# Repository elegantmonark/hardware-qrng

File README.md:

# Hardware QRNG Investigation

This is my attempt to investigate whether a circuit built around a reverse biased green LED, an amplifier and an Arduino can serve as a physical entropy source. ED-1 used an LM358; the newer ED-4A PCB specifies an MCP6002. The [contents](#contents) and [repository guide](#repositoryguide) point to the measurements, circuit revisions and analysis. Enjoy your time here :)) (BE SURE TO READ THE "IMPORTANT" SECTIONS!)

**Author:** Trishan Biswas  
**Project started:** December 2025  
**First complete demonstrator and dataset:** April 2026

| ED-1 bit balance and software comparison | ED-2 latest breadboard build |
|:---:|:---:|
|  |  |
| ED-1 output compared with a deterministic Mersenne Twister control. Similar results do not establish physical origin or security. | Latest documented ED-2 arrangement, retained as a development build rather than a validated entropy source. |

**ED-4A signal path simulation:** A small test signal is amplified to the expected
Arduino input range in an approximate ngspice model. The LED source remains to
be measured. [Simulation details](hardware/ED-4/pcb/ED4-A/simulation/README.md).

## Contents

- [MATLAB analysis](#matlab) · [ED-4A Arduino PCB](#ed4pcb) · [ED-4A PCB views](#pcbviews) · [ngspice checks](#ngspicechecks) · [Overview](#overview)
- [Quick terminology](#terminology) · [Development](#development) · [ED 1 results](#ed1results) · [Quantum triggers and a possible TRNG](#quantumtriggers) · [Limitations](#limits)
- [ED 2 circuit](#ed2circuit) · [ED 3 circuit](#ed3circuit) · [ED-4 PCB and printed enclosure](#ed4enclosure) · [Hardware photographs](#photographs) · [Repository guide](#repositoryguide)
- [Next work](#nextwork) · [Licence](#licence) · [Reproducing the analysis](#analysis) · [Collecting new data](#collection)

## MATLAB analysis

I used MATLAB to examine the original million sample Arduino capture through
signal traces, ADC distributions, a Hann windowed FFT, autocorrelation and bit
balance across consecutive blocks. The analysis runs without extra toolboxes.

The proportion of ones is 0.497767, but the raw ADC correlation at lag 1 is
0.9057 and the strongest spectral component repeats every 14.87 samples.
The extracted bits look nearly balanced while the original signal has clear
structure. That distinction guides the next round of circuit measurements.

The [MATLAB source and instructions](software/matlab/README.md) explain how to
repeat the analysis. The [saved results](results/ED-1/matlab/README.md) include
the report, correlation CSV and editable figure. The MATLAB R2026b Update 1
results matched the Python audit, including all 101 exported correlation rows.
These are descriptive checks, not proof of quantum origin or secure entropy.

## ED-4A Arduino PCB

The first ED-4 PCB is a two layer, 89 by 52 mm board for the enclosure already
printed. It brings the buffered reference, source selector, signal amplifier
and Arduino interface together with seven test points and a bottom ground fill.
The design uses through hole parts for assembly and inspection.

The [editable KiCad project](hardware/ED-4/pcb/ED4-A/ED4_A_Arduino.kicad_pro),
[schematic](hardware/ED-4/pcb/ED4-A/drawings/ED4_A_schematic.pdf) and
[board guide](hardware/ED-4/pcb/ED4-A/README.md) are available for review.
The revision B layout uses an MCP6002 and a standard 100k and 1k gain network.
It passes KiCad ERC, DRC and schematic parity checks. Circuit validation and
populated enclosure fit remain pending. The [purchase BOM](hardware/ED-4/pcb/ED4-A/BOM.csv)
records the chosen components.

I have also included the [JLCPCB Gerber ZIP, assembly BOM and placement file](hardware/ED-4/pcb/ED4-A/jlcpcb/README.md).
That assembly option covers 11 components. R3, R4, R6 and D1 would be fitted
by hand because they were unavailable in the assembly inventory. The removable
JP1 shunt is separate too. I may instead order the bare PCB and fit all the
components myself.

I also ran an [ngspice signal path check](hardware/ED-4/pcb/ED4-A/simulation/README.md)
with the PCB component values and a small injected test signal. The approximate
model shows the expected reference and gain at the Arduino input. It does not
model the LED noise or validate the entropy source.

ED-4A uses an external Arduino with a 5 V ADC interface. ED-4E is the planned
ESP32 revision and will have its own ADC and power interface review.

## ED-4A PCB views

These are KiCad views of the revision B design. They show the intended board
and component positions before manufacture. The 3D renders show R3, R4, R6
and D1 in place, although those parts are omitted from the optional JLCPCB
assembly order. C4 appears as a footprint because its 3D model is not shown.
The LED model is red in these views, but the BOM specifies a green LED.

### Routed layout

### Component renders

| Top view | Angled view |
|:---:|:---:|
|  |  |

The renders show the planned layout, not a built board or a confirmed fit in
the printed enclosure.

## ngspice checks

I used ngspice to test the ED-4A analogue path with known inputs before
building the board. The [netlists, figures and method](hardware/ED-4/pcb/ED4-A/simulation/README.md)
are in the simulation folder. They use the PCB values and an approximate op amp
model. None of these runs models the LED noise or proves that the circuit will
produce useful entropy.

The first check used a 2 mV peak signal at 1 kHz and showed about 100 times
gain at the Arduino input. I then grounded the input and added a 100 mV peak,
100 Hz ripple to the 5 V rail. In that model A0 still moved by about 160 mV
peak, so the actual supply and grounded control will need careful measurement.

I also compared 2 mV and 40 mV peak test inputs. The smaller signal stayed
within the Arduino input range, while the larger one reached both output
limits in the model. The LED signal amplitude has not been measured yet.

## Overview

The project is organised into four stages. ED stands for Entropy Demonstrator;
the table distinguishes the completed work, archived prototypes and planned builds.

| Stage | Purpose | Current state |
|---|---|---|
| **ED-1** | Prove that the full path from circuit to saved data and analysis could work | Complete and preserved |
| **ED-2** | Explore a documented two-stage analogue path and acquisition process | Completed and preserved as a breadboard investigation; reference loading found during bring-up and recorded |
| **ED-3** | Validate a simpler buffered reference circuit on breadboard, with optional perfboard transfer afterwards | Design documented; assembly and validation pending |
| **ED-4** | Custom PCB for the existing printed enclosure | ED-4A Arduino layout available for review; 89 by 52 mm; bench and populated fit checks pending. ED-4E ESP32 revision planned |

The name QRNG describes the research direction. The present evidence supports an experimental physical entropy source, not a certified quantum random number generator or a source suitable for cryptographic use.

The investigation asks three practical questions:

1. Does the circuit produce measurable physical noise?
2. Can useful digital bits be extracted from it consistently?
3. Do the results survive repeat captures, restarts and control experiments?

Statistical tests can describe a bitstream, but they cannot identify its physical origin on their own. The circuit, sampling process and possible interference must be studied alongside the output.

## Quick terminology

| Term | Meaning in this project |
|---|---|
| **Entropy source** | A physical process being investigated as a possible source of unpredictable variation |
| **ADC reading** | A number produced when the Arduino converts the measured circuit voltage into a digital value |
| **Least significant bit** | The final binary digit of an ADC reading, recorded here as a candidate random bit |
| **Bitstream** | The resulting sequence of zeros and ones |
| **Software control** | A deterministic Mersenne Twister sequence used for comparison, not a NIST reference generator |
| **ED** | Entropy Demonstrator |

The analysis checks balance, repetition, correlation and stability. A balanced output alone does not prove that the signal is quantum or secure.

## Development

I began the project in December 2025 because it combined semiconductor physics, analogue electronics, microcontroller sampling and Python analysis in one experiment.

In April 2026, ED-1 became the first complete demonstrator. It produced a saved sequence of one million ADC readings and one least significant bit from each reading. I then built a software control, generated comparison figures and ran exploratory statistical tests.

> [!IMPORTANT]
> The first result looked promising because the extracted bits were close to balanced. A later audit showed that the raw ADC sequence contained strong correlation and a repeating component. This did not make ED-1 useless. It made ED-1 a clear baseline and showed what the next version needed to improve.

ED-2 kept the original LED source idea but added a defined midpoint reference, two amplifier stages, clearer bias paths, supply decoupling and output protection. During systematic bring-up, the Stage A reference branch pulled the unbuffered midpoint from approximately 2.5 V to approximately 1.3 V. That result is preserved as part of the engineering record rather than presented as a validated improvement.

ED 3 starts again with a simpler topology. Its documented breadboard uses one
LM358 section to buffer the midpoint and the other as a signal amplifier. The
ED-4 PCB revision B uses a pin compatible MCP6002 and revised resistor values
to reduce input bias error. That component change needs its own bench checks.
After breadboard validation, the ED 3 circuit may also be transferred to
perfboard and checked again. ED-4 has a nominal 89 by 52 mm outline for the
enclosure already printed. The earlier
bare perfboard fit check establishes a starting board envelope; PCB tolerances,
component clearance and connector access still need checking.

## ED 1 results

The preserved April 2026 capture contains 1,000,000 samples.

| Measurement | Result |
|---|---:|
| Ones | 497,767 |
| Zeros | 502,233 |
| Proportion of ones | 0.497767 |
| Binary Shannon entropy | 0.9999856 bits per bit |
| Most common value estimate | 0.9935713 bits per bit |
| Raw ADC range | 0 to 760 |
| Raw ADC lag 1 correlation | 0.9057 |
| Dominant raw period | approximately 14.87 samples |
| Extracted bit lag 1 correlation | 0.00119 |

The bit balance was encouraging, but the raw ADC correlation showed that the analogue signal contained substantial structure. The exploratory NIST STS run also reported failures in Frequency, Runs and forward Cumulative Sums. These results are kept in the repository because they are part of the engineering record.

The full interpretation is recorded in [`docs/validation.md`](docs/validation.md).

## Quantum triggers and a possible TRNG

The idea is to use noise from a reverse biased semiconductor junction as the
physical input to a true random number generator (TRNG). Zener tunnelling is a
quantum process in which carriers cross the junction barrier. Avalanche
breakdown instead multiplies carriers through impact ionisation; a small,
stochastic carrier event can seed a much larger cascade. That makes tiny events
measurable in a suitable device. Signal size and entropy are different things,
though: a large, changing voltage is not automatically unpredictable.
[Analog Devices' breakdown explanation](https://wiki.analog.com/university/courses/electronics/text/chapter-14#zener_diodes)
distinguishes the Zener and avalanche regimes.

ED-4A biases an ordinary green LED through 10 MΩ from 3.3 V. I have not measured
its reverse current or shown that this LED reaches Zener or avalanche breakdown
at that bias. The board's amplifier has a simulated gain of about 100 for a
known test signal; an additional avalanche multiplication factor has not been
measured. For now this is a **candidate physical TRNG with a possible quantum
contribution**, rather than an established QRNG. [Diode tunnelling has been used
in a demonstrated QRNG](https://doi.org/10.1103/PhysRevApplied.11.034060), but
that result does not establish the mechanism in this LED.

The useful experiment is to measure the LED voltage and reverse current, then
compare the source with grounded input, resistor and covered LED controls over
repeat captures. That will show whether the junction adds measurable variation
before making a claim about where the unpredictable part comes from. The
[validation notes](docs/validation.md) spell out the remaining checks.

## Limitations

The present data cannot separate junction noise from Johnson–Nyquist noise in
resistors, low frequency flicker noise, amplifier and ADC noise, or movement of
the power supply. Thermal and flicker noise can be genuinely stochastic; the
issue is attributing the measured bits specifically to a quantum junction
process. Supply ripple and coupled interference can add repeatable structure
that looks like activity at the ADC. The [ngspice grounded-input check](hardware/ED-4/pcb/ED4-A/simulation/README.md)
shows why the reference and supply need measuring on the real board.

ED-1 contains one capture with strongly correlated raw ADC readings. ED-2
exposed a reference loading fault. ED-3 and the ED-4A PCB still need source and
control measurements. Near equal numbers of zeros and ones, a high marginal
Shannon entropy, or a large analogue signal do not establish an independent
entropy rate. [NIST SP 800-90B](https://doi.org/10.6028/NIST.SP.800-90B)
provides a framework for characterising an entropy source; this project has
not completed that validation.

> [!CAUTION]
> No output from this repository should be used for cryptographic keys, authentication, gambling, financial decisions or safety critical systems.

The [detailed limitations](docs/limitations.md), [safety notes](docs/safety.md)
and [security notes](SECURITY.md) give the test conditions and remaining gaps.

## ED 2 circuit

ED-2 uses the following signal path:

1. A green LED is connected as the proposed physical noise source.
2. A 2.5 V midpoint reference supports operation from a single 5 V supply.
3. Two LM358 noninverting stages amplify the alternating component of the signal.
4. A protected output feeds Arduino input A0.
5. The Arduino records each raw ADC code and its least significant bit.
6. A steady D7 indicator shows that the sampler is running without switching for every recorded bit.

The exact component values, breadboard positions, expected voltages and assembly order are documented in [`circuit.md`](circuit.md). The matching sampler is stored at [`firmware/ED-2/entropy_sampler_ed2.ino`](firmware/ED-2/entropy_sampler_ed2.ino).

ED-2 produced live ADC readings, but systematic probing exposed reference loading in the assembled topology. ED-2 is completed and preserved as an investigation with a documented design fault. It has no published validation dataset and is not a verified entropy source.

## ED 3 circuit

ED-3 uses a buffered midpoint reference and one signal amplifier. The reduced
topology removes the second signal-gain stage and prevents the gain network from
directly loading the 10 kOhm midpoint divider.

The proposed component values, electrical netlist and staged bring-up sequence
are documented in [`hardware/ED-3/circuit.md`](hardware/ED-3/circuit.md). The
matching sampler is stored at
[`firmware/ED-3/entropy_sampler_ed3.ino`](firmware/ED-3/entropy_sampler_ed3.ino).
ED-3 will not be described as working until its reference, amplifier baseline,
source controls and repeat captures have been checked.

An optional perfboard version remains part of ED 3. It follows breadboard
validation and must repeat the electrical checks and control captures after
transfer.

## ED-4 PCB and printed enclosure

ED-4 combines a custom routed PCB with the existing two part enclosure. The base
was printed successfully, and an 89 by 52 mm bare perfboard fits between its
locating features. The PCB will use that nominal envelope, with a target
thickness of 1.6 mm. Its final fit must account for print tolerances, support
rails, solder joints, component height and cable access.

| Dimension | Value |
|---|---:|
| Nominal PCB target | 89 by 52 mm, 1.6 mm thick |
| Internal space | 105 by 68 by 34 mm |
| Approximate assembled exterior | 109.8 by 72.8 by 40 mm |
| Board support height | 8 mm |
| Clearance above the board | approximately 24.4 mm |
| Cable opening | 26 by 12 mm |

The existing cable opening was sized for an Arduino harness. The final PCB
connector and acquisition interface will follow the validated ED 3 circuit.

The [PCB plan](hardware/ED-4/pcb-plan.md) records the mechanical constraints,
intended features and checks required before fabrication.

The [ED-4A Arduino PCB](hardware/ED-4/pcb/ED4-A/README.md) is the current routed
review design. ED-4E will cover ESP32 separately. The board outline is shared;
the ADC and power interfaces must be reviewed for each revision.

The editable source, printable files, dimensions and print guidance are available in the [ED-4 CAD directory](hardware/ED-4/cad/README.md).

The current KiCad evidence is the [ED-4A schematic and routed PCB](hardware/ED-4/pcb/ED4-A/README.md).
The layout passes ERC, DRC and schematic parity checks. The earlier unfinished
perfboard placement draft has been superseded by this design.

| Printed ED-4 enclosure base | Initial perfboard fit check |
|:---:|:---:|
|  |  |
| The first physical print of the enclosure base and internal locating features. | An 89 by 52 mm bare perfboard establishing the initial envelope for the planned PCB. |

## Hardware photographs

The photographs keep the demonstrators visually separate so their wiring and mechanical progress cannot be mistaken for the same revision.

| ED-1 first demonstrator | ED-2 improved breadboard |
|---|---|
|  |  |
| Original breadboard used for the first complete acquisition and analysis path. | Wider view of the latest documented ED-2 breadboard with its Arduino connection. |

Additional views and captions are stored in the [ED-1 hardware notes](hardware/ED-1/README.md), [ED-2 hardware notes](hardware/ED-2/README.md) and [ED-4 enclosure notes](hardware/ED-4/README.md).

## Repository guide

| Location | Contents |
|---|---|
| [`data/`](data/README.md) | Preserved captures, controls and integrity hashes |
| [`docs/`](docs/development-log.md) | Development history, theory, limits, safety and validation plans |
| [`figures/ED-1/`](figures/ED-1/) | Figures generated from the April 2026 capture |
| [`firmware/`](firmware/README.md) | Arduino samplers separated by demonstrator |
| [`hardware/`](hardware/README.md) | Photographs, build records, the ED-3 circuit and ED-4 CAD |
| [`results/`](results/README.md) | The ED-1 audit and exploratory statistical output |
| [`software/`](software/) | Collection, analysis, comparison and extraction tools |
| [`tests/`](tests/) | Data, link, asset, analysis and CAD integrity tests |

The artwork made from the ED-1 bits is prepared as a [separate Bitstream Art project](https://github.com/elegantmonark/qrng-bitstream-art).

## Next work

1. Assemble ED-3 in tested stages, beginning with the buffered reference.
2. Record the final component values, node checks and build photographs.
3. Capture ED-3 controls and source runs across independent restarts.
4. Compare its raw signal structure, bias, correlation and stability with ED-1.
5. Establish a conservative entropy estimate before introducing conditioning.
6. Select the acquisition architecture from evidence; an Arduino, ESP32, or external ADC must not be treated as the entropy source.
7. Optionally transfer the validated ED 3 circuit to perfboard and repeat its checks.
8. Build the ED-4 PCB within the printed enclosure's 89 by 52 mm board envelope.

## Licence

The hardware, analysis and documentation are released under the Apache License 2.0 in [`LICENSE`](LICENSE).

## Reproducing the analysis

Install the Python dependencies from the repository root:

```bash
python -m pip install -r requirements.txt
```

Run the repository tests:

```bash
python -m unittest discover -s tests -v
```

Regenerate the ED-1 diagnostics and comparison:

```bash
python software/analyser.py
python software/compare.py
```

For the MATLAB version, see the [analysis section](#matlab) and its
[run instructions](software/matlab/README.md).

The exploratory NIST wrapper requires a separately installed NIST STS executable. Read [`docs/validation.md`](docs/validation.md) before interpreting its output.

## Collecting new data

After ED-3 passes bring-up, upload the ED-3 sampler, confirm the serial port and run:

```bash
python software/collector.py --port COM3 --samples 1000000
```

Replace `COM3` with the port used by the Arduino. The collector writes a new timestamped CSV and a JSON metadata file under `data/ED-3/runs/`. A capture should not be published until the circuit values, firmware version, conditions and file hash have been recorded.

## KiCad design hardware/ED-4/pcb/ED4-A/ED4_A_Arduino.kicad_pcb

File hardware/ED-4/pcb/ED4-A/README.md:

# ED4 A Arduino prototype, revision B

This board carries the proposed ED 3 buffered reference and signal amplifier
inside the printed ED 4 enclosure. It uses through hole parts and an external
Arduino for power and data capture. The PCB is 89 by 52 mm and 1.6 mm thick.

The layout is a review prototype. The circuit has not yet been validated on
breadboard or PCB, and populated fit has not been checked in the actual print.
Check the circuit and enclosure fit before ordering a populated prototype.

## Open the project

Open [ED4_A_Arduino.kicad_pro](ED4_A_Arduino.kicad_pro) in KiCad 10. The
[schematic](ED4_A_Arduino.kicad_sch) and [PCB](ED4_A_Arduino.kicad_pcb) are
editable. The circuit values follow the current ED 3 proposal, with a local
10 uF supply capacitor and a source/control selector added for testing. This
revision uses an MCP6002 op amp and standard resistor values chosen for the
actual circuit rather than parts already on hand.

## Files for review

| File | Purpose |
| --- | --- |
| [Schematic PDF](drawings/ED4_A_schematic.pdf) | Connected circuit and pin labels |
| [Assembly PDF](drawings/ED4_A_assembly.pdf) | Component positions and enclosure rail strips |
| [BOM](BOM.csv) | Selected manufacturer parts and board footprints |
| [JLCPCB order files](jlcpcb/README.md) | Gerber ZIP, assembly BOM and placement file |

KiCad 10.0.1 reports 0 ERC violations, 0 DRC violations, 0 unconnected items
and 0 schematic parity issues. An independent pin contract check agreed with
the schematic and board. These checks do not replace bench validation.

The [ngspice signal path check](simulation/README.md) uses an injected test
signal and an approximate op amp model to check the intended reference and
amplifier response. It does not model the LED noise or validate the PCB in
hardware.

The full BOM lists the original part choices. The JLCPCB assembly BOM uses
available alternatives for C1, C2 and C3, and leaves R3, R4, R6 and D1 for
hand assembly. Check part selection and the actual enclosure fit before
ordering. A successful layout check does not establish that the LED produces
useful entropy in this circuit.

## Arduino connector

J1 is a straight 2.54 mm pin header. Pad 1 is square and the signals are marked
on the board. Check pin numbers in KiCad before attaching the harness.

| J1 pin | Signal | Connection |
| --- | --- | --- |
| 1 | 5V | Arduino 5 V supply |
| 2 | 3V3 | Arduino 3.3 V source bias supply |
| 3 | GND | Common ground |
| 4 | A0 | Analogue output for a 5 V Arduino ADC interface |

Arduino AREF is left disconnected. Do not connect the output directly to an
ESP32 ADC. The future ED4 E revision will handle that interface separately.

## Source and control selector

JP1 is a three pin header with one removable shunt. Change its position with
power disconnected.

| Shunt | Connection | Use |
| --- | --- | --- |
| Pins 1 and 2 | LED source to the coupling capacitor | Source capture |
| Pins 2 and 3 | Coupling capacitor input to ground | Grounded AC input control |
| No shunt | Coupling capacitor input open | Open input diagnostic only |

The grounded control changes the input condition and does not isolate every
noise contribution. D1 remains biased through R3 in either shunt position.
Use separate covered LED, resistor control and restart captures as well.

D1 pad 1 is the cathode and pad 2 is the anode. Its reverse biased connection
follows the experimental ED 3 circuit. The listed Kingbright WP7113GD is a
physical part choice, not a validated entropy source. Its reverse behavior at
3.3 V must be measured before a functional claim can be made.

## Test points

| Point | Signal |
| --- | --- |
| TP1 | Raw midpoint reference |
| TP2 | Buffered midpoint reference |
| TP3 | LED source node |
| TP4 | Amplifier input |
| TP5 | Amplifier output before R7 |
| TP6 | Arduino A0 output after R7 |
| TP7 | Ground |

Probing the high impedance source node can load it. Record the probe and
measurement setup when interpreting the source signal.

## Mechanical review

The board outline matches the envelope used for the enclosure fit check.
The marked rail contact strips are on the drawing layer. Check solder joints
against the rails, components against the corner guides and lid, and the cable
bend against the 26 by 12 mm opening. No mounting holes have been assumed.

The [enclosure CAD](../../cad/README.md) preserves the existing printed geometry.
Two rule areas prohibit pads and vias where the printed rails touch the board.
The bottom copper layer has a filled ground return.

## Board mark

The front silkscreen carries a compact QRNG mark: a Q ring flowing into three
digital bit marks. It is an editable group named `QRNG logo` in the PCB editor.
The [SVG](../assets/qrng-logo.svg) is included for reuse in project documents.

## First bench checks

1. Check part values, U1 orientation, D1 polarity and capacitor polarity.
2. With the supply off, inspect for shorts and verify J1 pin order.
3. Power the board with current limiting and check the supply rails.
4. Measure TP1 and TP2. Confirm the reference remains stable under load.
5. Select the grounded AC control and check amplifier baseline and headroom.
6. Inspect for clipping or oscillation before connecting the Arduino ADC.
7. Compare source, control and restart captures using the original raw samples.

The nominal gain is 1 + 100k / 1k = 101. R4 is 100k and R7 is 1k. The
MCP6002 has much lower input bias than the earlier LM358 choice, which matters
for the high impedance input. Its offset still affects the baseline, so check
TP5 for clipping and stability. The [Microchip datasheet](https://ww1.microchip.com/downloads/aemDocuments/documents/MSLD/ProductDocuments/DataSheets/MCP6001-1R-1U-2-4-1-MHz-Low-Power-Op-Amp-DS20001733L.pdf)
documents the PDIP pinout and electrical limits. The schematic uses the
KiCad LM2904 graphical symbol because its three units have the same pin map;
the fitted component is the MCP6002-I/P in the BOM and PCB.

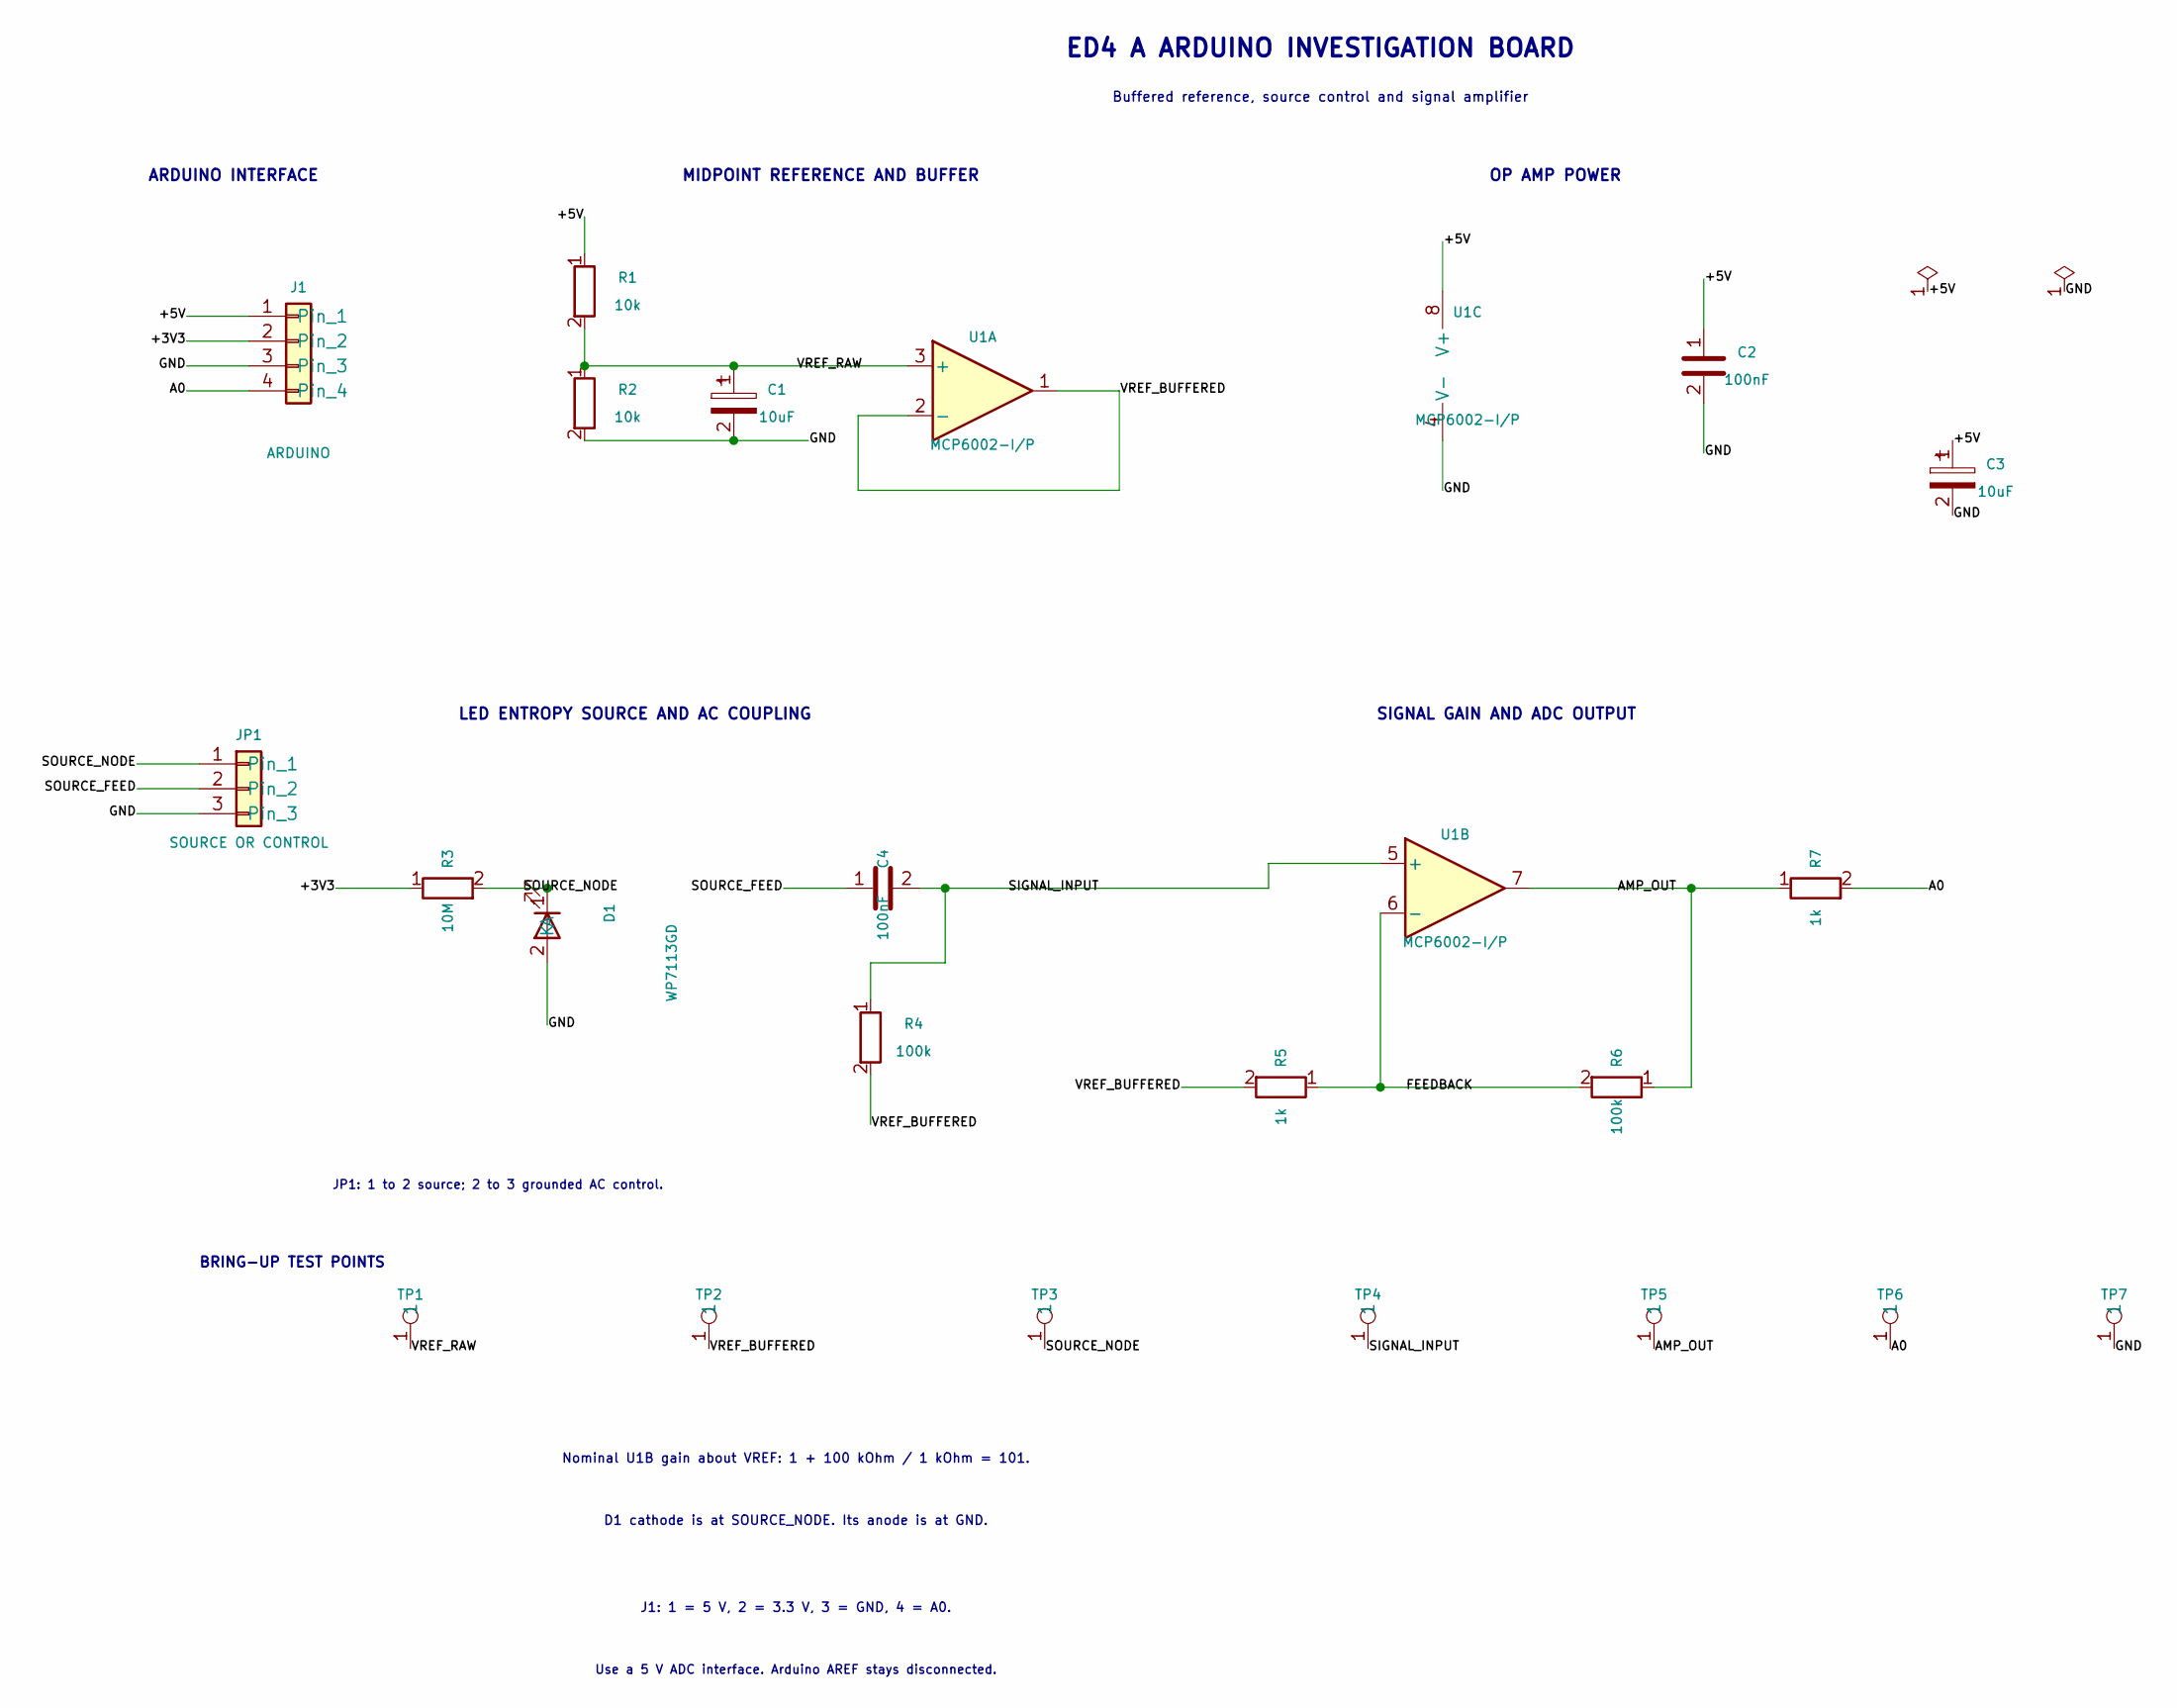
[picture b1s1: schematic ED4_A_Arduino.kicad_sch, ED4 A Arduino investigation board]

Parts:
C1, C3: 10uF; CP_Radial_D5.0mm_P2.00mm
C2: 100nF; C_Disc_D5.0mm_W2.5mm_P2.50mm
C4: 100nF; C_Rect_L7.2mm_W2.5mm_P5.00mm
D1: WP7113GD; LED_D5.0mm
J1: ARDUINO; PinHeader_1x04_P2.54mm_Vertical
JP1: SOURCE OR CONTROL; PinHeader_1x03_P2.54mm_Vertical
R1, R2: 10k; R_Axial_DIN0207_L6.3mm_D2.5mm_P10.16mm_Horizontal
R3: 10M; R_Axial_DIN0207_L6.3mm_D2.5mm_P10.16mm_Horizontal
R4, R6: 100k; R_Axial_DIN0207_L6.3mm_D2.5mm_P10.16mm_Horizontal
R5, R7: 1k; R_Axial_DIN0207_L6.3mm_D2.5mm_P10.16mm_Horizontal
TP1: VREF_RAW; TestPoint_THTPad_D2.0mm_Drill1.0mm
TP2: VREF_BUFFERED; TestPoint_THTPad_D2.0mm_Drill1.0mm
TP3: SOURCE_NODE; TestPoint_THTPad_D2.0mm_Drill1.0mm
TP4: SIGNAL_INPUT; TestPoint_THTPad_D2.0mm_Drill1.0mm
TP5: AMP_OUT; TestPoint_THTPad_D2.0mm_Drill1.0mm
TP6: A0; TestPoint_THTPad_D2.0mm_Drill1.0mm
TP7: GND; TestPoint_THTPad_D2.0mm_Drill1.0mm
U1: MCP6002-I/P; DIP-8_W7.62mm

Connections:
/+3V3: J1.2, R3.1
/+5V: C2.1, C3.1, J1.1, R1.1, U1.8 (V+)
/A0: J1.4, R7.2, TP6.1
/AMP_OUT: R6.1, R7.1, TP5.1, U1.7
/FEEDBACK: R5.1, R6.2, U1.6 (-)
/GND: C1.2, C2.2, C3.2, D1.2 (A), J1.3, JP1.3, R2.2, TP7.1, U1.4 (V-)
/SIGNAL_INPUT: C4.2, R4.1, TP4.1, U1.5 (+)
/SOURCE_FEED: C4.1, JP1.2
/SOURCE_NODE: D1.1 (K), JP1.1, R3.2, TP3.1
/VREF_BUFFERED: R4.2, R5.2, TP2.1, U1.1, U1.2 (-)
/VREF_RAW: C1.1, R1.2, R2.1, TP1.1, U1.3 (+)

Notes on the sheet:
ED4 A ARDUINO INVESTIGATION BOARD
Buffered reference, source control and signal amplifier
ARDUINO INTERFACE
MIDPOINT REFERENCE AND BUFFER
OP AMP POWER
LED ENTROPY SOURCE AND AC COUPLING
JP1: 1 to 2 source; 2 to 3 grounded AC control.
SIGNAL GAIN AND ADC OUTPUT
BRING-UP TEST POINTS
Nominal U1B gain about VREF: 1 + 100 kOhm / 1 kOhm = 101.
D1 cathode is at SOURCE_NODE. Its anode is at GND.
J1: 1 = 5 V, 2 = 3.3 V, 3 = GND, 4 = A0.
Use a 5 V ADC interface. Arduino AREF stays disconnected.

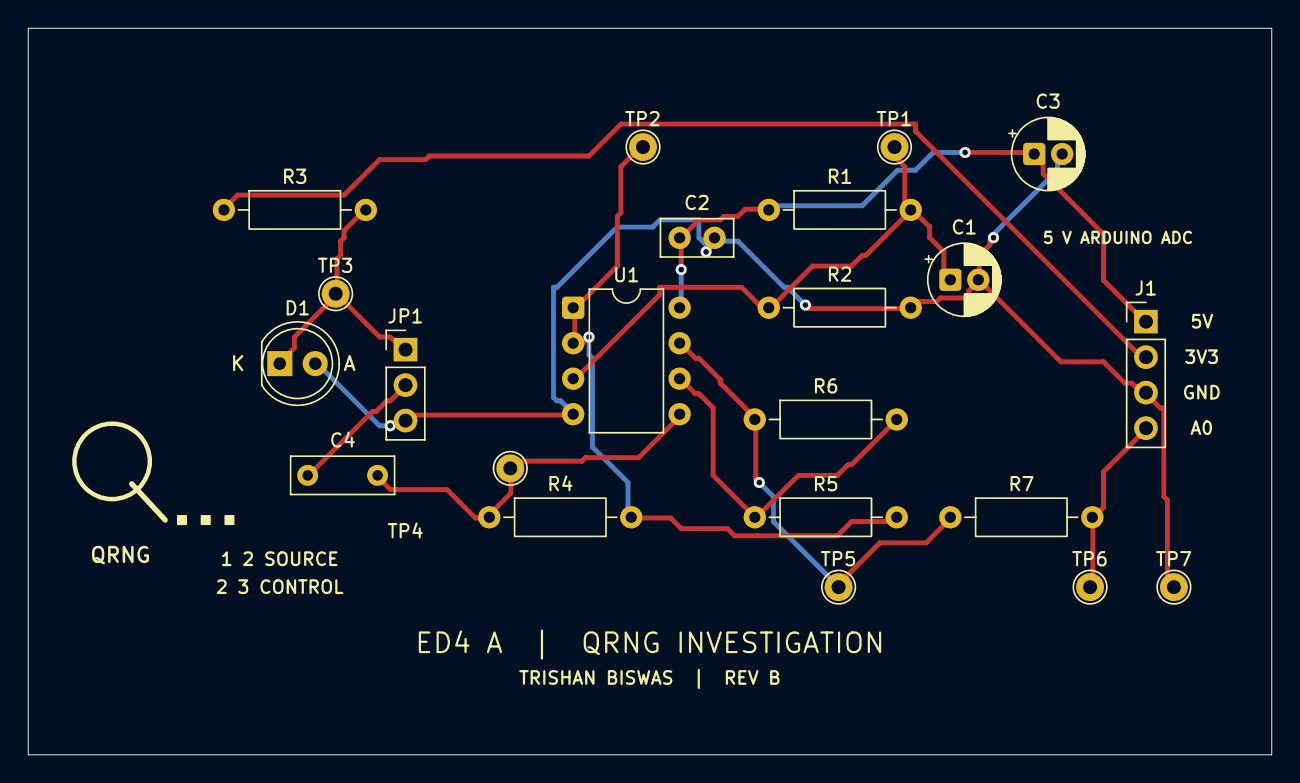
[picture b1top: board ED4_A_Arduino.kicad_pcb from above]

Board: 2 copper layers, 89.0 x 52.0 mm, 22 parts (0 on the bottom side), 11 nets.

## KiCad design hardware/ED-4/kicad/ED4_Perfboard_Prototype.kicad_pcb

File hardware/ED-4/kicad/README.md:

# ED-4 KiCad perfboard prototype

This directory contains an editable schematic and placement draft for transferring the proposed ED-3 buffered-reference circuit to the 89 by 52 mm ED-4 perfboard.

> [!IMPORTANT]
> This is a prototype layout, not an assembly-ready or validated circuit. ED-3 must first pass the documented voltage checks and controlled captures. The final ED-4 wiring should then be updated to match the circuit that was actually verified.

## Files

- `ED4_Perfboard_Prototype.kicad_pro`: KiCad project file.
- `ED4_Perfboard_Prototype.kicad_sch`: editable circuit schematic.
- `ED4_Perfboard_Prototype.kicad_pcb`: editable 89 by 52 mm perfboard placement.
- `exports/ed4-perfboard-prototype-isometric.png`: isometric KiCad render of the proposed component placement.
- `exports/ed4-perfboard-prototype-top.png`: top-view KiCad render for documentation.
- `exports/ed4-perfboard-prototype-bottom.png`: underside KiCad render for placement inspection.
- `exports/ed4-perfboard-prototype-layout.svg`: scalable 2D KiCad layout export.
- `exports/ed4-perfboard-prototype-schematic.pdf`: KiCad schematic export.
- `exports/ed4-perfboard-prototype-schematic.png`: quick schematic preview.
- `exports/ed4-schematic-erc.rpt`: KiCad electrical-rules report.
- `exports/ed4-perfboard-drc.rpt`: board-rules report for the unfinished perfboard model.
- `generate_ed4_perfboard.py`: reproducible board generator for KiCad's bundled Python environment.
- `generate_ed4_schematic.py`: reproducible schematic generator using KiUtils.
- `requirements-kicad.txt`: version-pinned schematic generator dependency.

## What the draft includes

- 35 by 20 hole grid at 2.54 mm pitch inside an 89 by 52 mm outline;
- LM358N in a DIP-8 package;
- 10 kOhm midpoint divider and 10 uF reference capacitor;
- LM358 voltage follower for `VREF_BUFFERED`;
- reverse-biased green LED source with a 10 MOhm feed resistor;
- 100 nF input coupling and supply decoupling capacitors;
- 330 kOhm bias and feedback resistors, 4.4 kOhm gain resistor and 690 Ohm A0 protection resistor;
- labelled test points for staged bring-up; and
- a four-wire Arduino connection for 5 V, 3.3 V, GND and A0.

Component placement and net assignments are included. Permanent jumper and solder-side routing is deliberately not finalised because ED-3 has not yet been electrically validated.

| Isometric placement render | Connected circuit schematic |
|:---:|:---:|
|  |  |

The schematic passes KiCad ERC with 0 errors and 0 warnings. This checks schematic consistency, not whether the proposed entropy source will perform as intended in hardware.

The board renders are placement previews. They are not wiring diagrams and must not be used as the sole assembly reference. The current DRC report contains expected violations because the model includes the complete drilled perfboard grid and does not yet include the final solder-side links. It should not be interpreted as a fabrication-ready routed PCB.

## Regenerating the board

From this directory on Windows:

```powershell
& "C:\Program Files\KiCad\10.0\bin\python.exe" .\generate_ed4_perfboard.py
```

Open `ED4_Perfboard_Prototype.kicad_pro` in KiCad 10 after generation. Before physical assembly, check the installed component dimensions, confirm LED polarity, rerun ERC and DRC, and reconcile every net against the verified breadboard.

To regenerate the schematic, install its small file-format dependency and run:

```powershell
python -m pip install -r .\requirements-kicad.txt
python .\generate_ed4_schematic.py
& "C:\Program Files\KiCad\10.0\bin\kicad-cli.exe" sch upgrade --force .\ED4_Perfboard_Prototype.kicad_sch
```

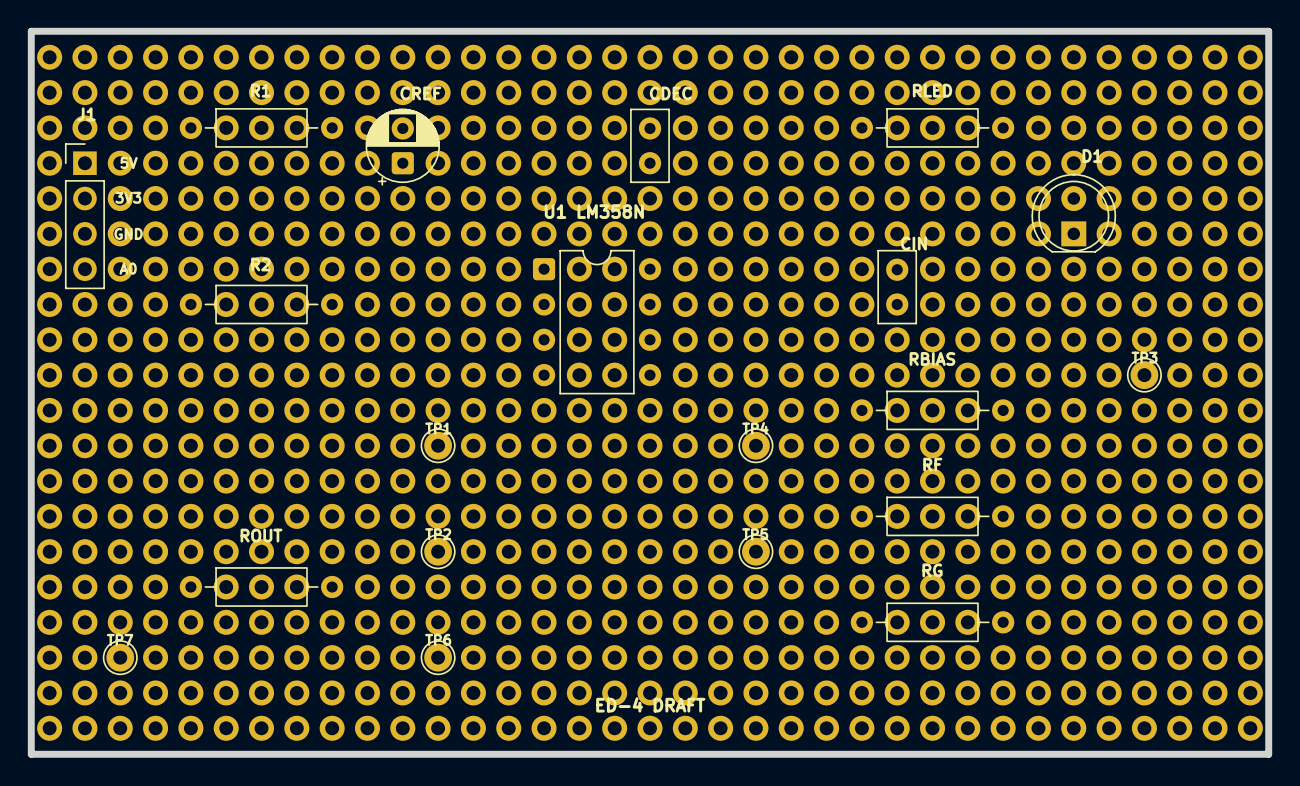
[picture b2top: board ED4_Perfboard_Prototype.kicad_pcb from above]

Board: 2 copper layers, 89.0 x 52.0 mm, 21 parts (0 on the bottom side), 10 nets, no tracks yet.

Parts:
CDEC: 100 nF; C_Disc_D5.0mm_W2.5mm_P2.50mm
CIN: 100 nF; C_Disc_D5.0mm_W2.5mm_P2.50mm
CREF: 10 uF; CP_Radial_D5.0mm_P2.50mm
D1: GREEN SOURCE LED; LED_D5.0mm
GRID1: 89x52 mm perfboard, 2.54 mm pitch
J1: ARDUINO; PinHeader_1x04_P2.54mm_Vertical
R1, R2: 10 kOhm; R_Axial_DIN0207_L6.3mm_D2.5mm_P10.16mm_Horizontal
RBIAS: 330 kOhm; R_Axial_DIN0207_L6.3mm_D2.5mm_P10.16mm_Horizontal
RF: 330 kOhm; R_Axial_DIN0207_L6.3mm_D2.5mm_P10.16mm_Horizontal
RG: 4.4 kOhm; R_Axial_DIN0207_L6.3mm_D2.5mm_P10.16mm_Horizontal
RLED: 10 MOhm; R_Axial_DIN0207_L6.3mm_D2.5mm_P10.16mm_Horizontal
ROUT: 690 Ohm; R_Axial_DIN0207_L6.3mm_D2.5mm_P10.16mm_Horizontal
TP1: VREF RAW; TestPoint_THTPad_D2.0mm_Drill1.0mm
TP2: VREF BUFFERED; TestPoint_THTPad_D2.0mm_Drill1.0mm
TP3: SOURCE; TestPoint_THTPad_D2.0mm_Drill1.0mm
TP4: SIGNAL INPUT; TestPoint_THTPad_D2.0mm_Drill1.0mm
TP5: AMP OUTPUT; TestPoint_THTPad_D2.0mm_Drill1.0mm
TP6: A0; TestPoint_THTPad_D2.0mm_Drill1.0mm
TP7: GND; TestPoint_THTPad_D2.0mm_Drill1.0mm
U1: LM358N; DIP-8_W7.62mm

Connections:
+3V3: J1.2, RLED.1
+5V: CDEC.1, J1.1, R1.1, U1.8
A0: J1.4, ROUT.2, TP6.1
AMP_OUT: RF.1, ROUT.1, TP5.1, U1.7
FEEDBACK: RF.2, RG.1, U1.6
GND: CDEC.2, CREF.2, D1.2, J1.3, R2.2, TP7.1, U1.4
SIGNAL_INPUT: CIN.2, RBIAS.1, TP4.1, U1.5
SOURCE_NODE: CIN.1, D1.1, RLED.2, TP3.1
VREF_BUFFERED: RBIAS.2, RG.2, TP2.1, U1.1, U1.2
VREF_RAW: CREF.1, R1.2, R2.1, TP1.1, U1.3

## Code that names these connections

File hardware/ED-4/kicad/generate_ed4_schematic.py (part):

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    add_wire(schematic, cref["1"], (cref["1"][0], vref_y))
    add_junction(schematic, r2["1"][0], vref_y)
    add_junction(schematic, cref["1"][0], vref_y)
    add_label(schematic, "VREF_RAW", 91.44, vref_y)

    ground_y = max(r2["2"][1], cref["2"][1])
    add_wire(
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    add_wire(schematic, rled["2"], cin["1"])
    add_wire(schematic, d1["1"], (d1["1"][0], source_y))
    add_junction(schematic, d1["1"][0], source_y)
    add_label(schematic, "SOURCE_NODE", 68.58, source_y)
    add_wire(schematic, d1["2"], (d1["2"][0], d1["2"][1] + 6.35))
    add_label(schematic, "GND", d1["2"][0], d1["2"][1] + 6.35)

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        (signal_corner_x, u1b["5"][1]),
        u1b["5"],
    )
    add_label(schematic, "SIGNAL_INPUT", 113.03, cin["2"][1])
    add_wire(
        schematic,
        (rbias["1"][0], cin["2"][1]),
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    )
    add_wire(schematic, (u1b["6"][0], feedback_y), rf["2"])
    add_junction(schematic, u1b["6"][0], feedback_y)
    add_label(schematic, "FEEDBACK", 153.67, feedback_y)
    add_wire(
        schematic,
        rg["2"],
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        rf["1"],
    )
    add_junction(schematic, output_branch_x, source_y)
    add_label(schematic, "AMP_OUT", 175.26, source_y)
    add_wire(
        schematic,
        rout["2"],
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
